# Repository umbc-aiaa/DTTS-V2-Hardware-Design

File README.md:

# DTTS V2

This repo houses the hardware design and associated documentation for the SUAS Dynamic Thrust Test Stand(DTTS) V2.
The new board is designed to be more intuitive to use and more robust against failures like over voltage, shorts, etc.
The V2 board also integrates all sensors and ICs in a single solution.

## System Diagram
```mermaid
graph LR;
LC[<b>Load Cell</b></br>Uses a Wheatstone Bridge to provide a differential voltage signal to the ADC.];
CS[<b>Current Sensor</b></br>Current sensing is implemented with a shunt resistor with differential input feeding into the ADC.];
VS[<b>Voltage Sensor</b></br>Voltage sensing circuit is implemented as a simple resistor voltage divider.];
ADC["<b>Analog-to-Digital Converter (ADC)</b></br>Converts single mode and differential analog signals into a digital format."];
MC[<b>ESP32 S3 WROOM 1</b></br>Controls esc for the motor, collects measurements, and communcates them over WiFi.];
ESC[<b>Electronic Speed Controller</b><br />Converts DC from battery to 3-phase AC for motor.]

GUI[<b>Front End UI</b></br>A front end GUI collects measurements and makes user interaction simple.];

LC --> ADC;
CS --> ADC;
VS --> ADC;

ADC --> MC;

MC -- PWM --> ESC;

GUI <== WiFi ==> MC;

ADC ~~~ GUI;
```

## Working Specs
- Battery Voltage $\leq$ 50 V.
- Max ESC Current $\leq$ 90 A.
- Using 6 AWG wire for battery.
- Must at minimum measure battery voltage, batter to ESC current, and Motor Thrust
- All circuitry must run off of a single battery -- the one plugged into the ESC
- Preferable to have auto-trimming and gain calibration on voltage sense circuity.

## Component Selection (Draft!)

### Power Supply
There are some different approaches to this. If we were using a seperate battery for this, then we could have just used a linear regulator, but if we want to use the motor battery, this voltage may range from 12 to 60 V. So we probably need to use a buck converter. We could also use a hybrid design (i.e. 12-60V input down to 4.5V with a buck converter and 4.5V to 3.3V with an LDO). This may complicate things a little, but it's a very good choice in terms of noise and is also fairly efficient.

1. ~~[Diodes Incorporated AP66200](https://www.diodes.com/assets/Datasheets/AP66200.pdf) Buck controller.~~
2. [TI LMR51625](https://www.ti.com/lit/ds/symlink/lmr51625.pdf?ts=1742888310253&ref_url=https%253A%252F%252Fwww.ti.com%252Fsitesearch%252Fen-us%252Fdocs%252Funiversalsearch.tsp%253FlangPref%253Den-US%2526nr%253D3%2526searchTerm%253DLMR51625XDDCR) Buck Controller (preferred).
  a. Also, if using TI ICs for power conversion, check out [Webench Designer](https://webench.ti.com/power-designer/)

**All regulated power rails must have a zener diode of appropriate voltage to pull lines down if they have too high of a voltage.**
We should run some simulations to ensure the zener diode is enough for protecting regulated lines if battery is shorted to them or if
we need to have something else. We may also want to consider adding a fuse to the power rail since the zener diode will short to ground
and pull a lot of current.

## Voltage Protection on Signal Pins
For signal pins, zener diodes may work, but there are options for more precise control like Schottkey diodes. These can also provide reverse polarity protection if configured correctly, so this is the solution we will use. Here are some options for diodes that may work. The Rohm diode has a lower forward drop, which is good for protecting against over-voltage, but it has a low reverse voltage rating which is worse for reverse-polarity protection. The opposite is true for the Toshiba diode. We may need to look for other diodes that have the adequate reverse voltage rating(60V) and a low drop(ideally $\leq$ 300mV).
1. [Toshiba CUS10S30 Schottkey Diodes](https://toshiba.semicon-storage.com/info/CUS10S30_datasheet_en_20140407.pdf?did=14077&prodName=CUS10S30) for signal over-voltage protection.\
  a. [Rohm RB520CM-60 Schottkey Diode](https://fscdn.rohm.com/en/products/databook/datasheet/discrete/diode/schottky_barrier/rb520cm-60t2r-e.pdf) Alternative to (1) with higher reverse voltage

### Analog to Digital Converter
This component converts analog voltages(i.e. voltages that are not strictly interpretted as a `0` or a `1`) into a digital format(i.e. `0`'s and `1`'s). This allows software on the esp32 to read and store analog voltages as numbers or percents and communicate these values over WiFi or another transport medium to the GUI for the user. Since we are using a load cell, this needs a sensative ADC, and hence we choose to use a 24-bit chip. These are some options worth considering:

1. [Microchip MCP3564R](https://ww1.microchip.com/downloads/aemDocuments/documents/APID/ProductDocuments/DataSheets/MCP3561_2_4R-Data-Sheet-DS200006391C.pdf) has four channels, meaning we can use this for all three sensors (battery voltage, battery current, and motor thrust).

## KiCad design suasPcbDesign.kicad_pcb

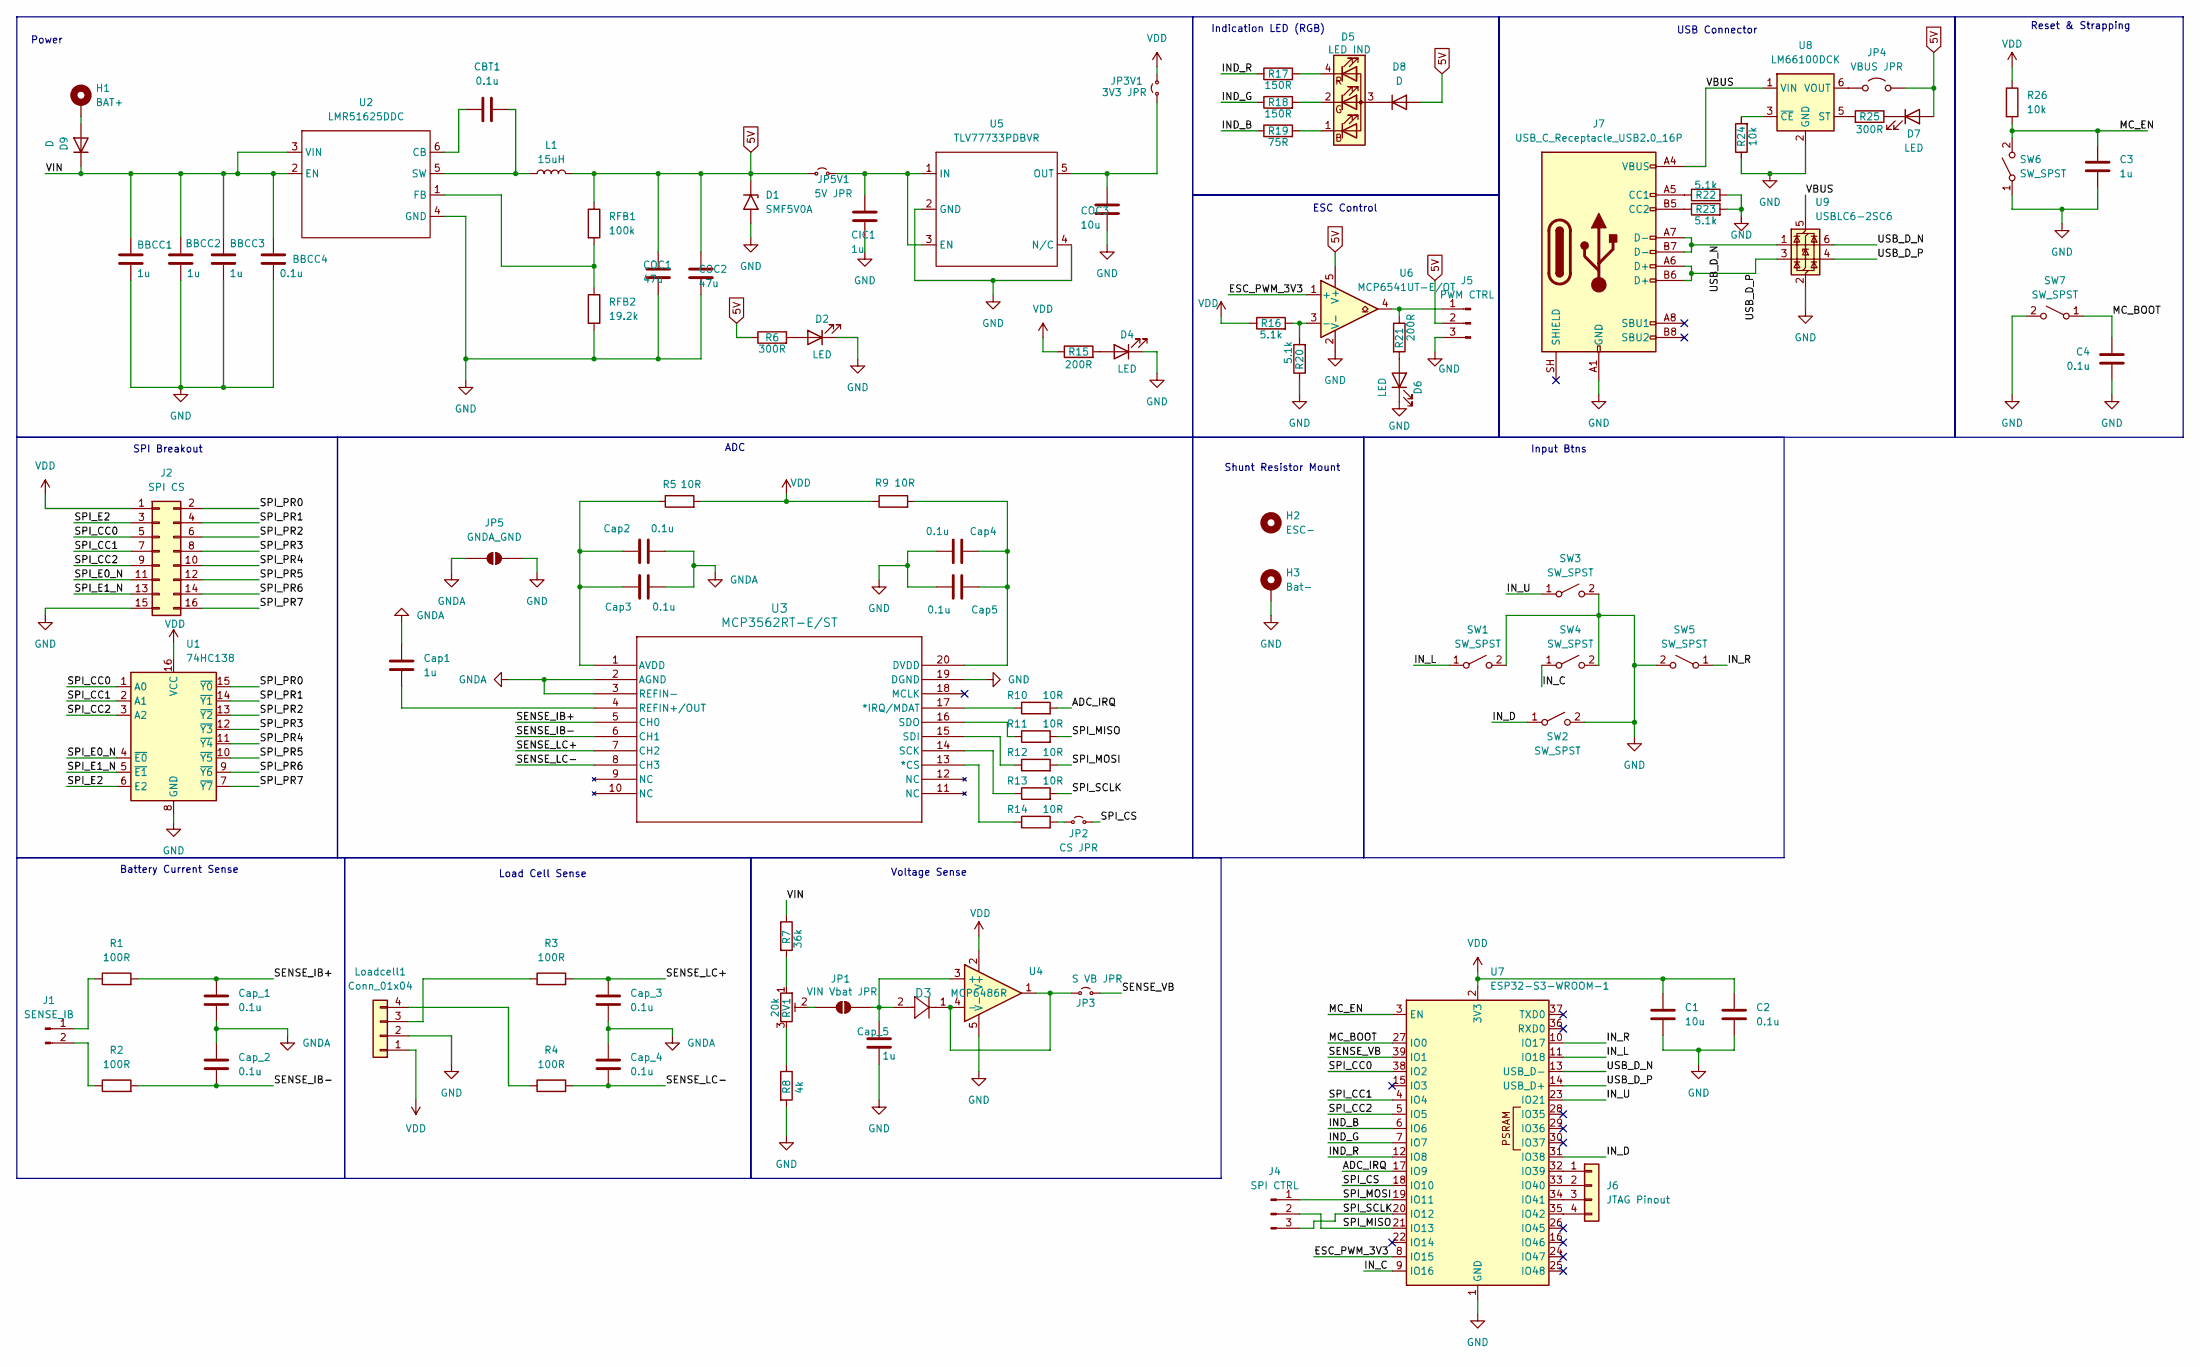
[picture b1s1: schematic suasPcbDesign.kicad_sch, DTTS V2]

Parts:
BBCC1, BBCC2, BBCC3: 1u; C_0603_1608Metric_Pad1.08x0.95mm_HandSolder
BBCC4: 0.1u; C_0603_1608Metric_Pad1.08x0.95mm_HandSolder
C1: 10u; C_0603_1608Metric_Pad1.08x0.95mm_HandSolder
C2, C4: 0.1u; C_0603_1608Metric_Pad1.08x0.95mm_HandSolder
C3: 1u; C_0603_1608Metric_Pad1.08x0.95mm_HandSolder
CBT1: 0.1u; C_0603_1608Metric_Pad1.08x0.95mm_HandSolder
CIC1: 1u; C_0603_1608Metric_Pad1.08x0.95mm_HandSolder
COC1, COC2: 47u; C_0603_1608Metric_Pad1.08x0.95mm_HandSolder
COC3: 10u; C_0603_1608Metric_Pad1.08x0.95mm_HandSolder
Cap1: 1u; C_0603_1608Metric_Pad1.08x0.95mm_HandSolder
Cap2, Cap3, Cap4, Cap5: 0.1u; C_0603_1608Metric_Pad1.08x0.95mm_HandSolder
Cap_1, Cap_2, Cap_3, Cap_4: 0.1u; C_0603_1608Metric_Pad1.08x0.95mm_HandSolder
Cap_5: 1u; C_0603_1608Metric_Pad1.08x0.95mm_HandSolder
D1: SMF5V0A; D_SOD-123
D2, D4, D6, D7: LED; LED_0603_1608Metric_Pad1.05x0.95mm_HandSolder
D3: CUS520_H3F; USC_TOS
D5: LED IND; LED_D5.0mm-4_RGB
D8, D9: D; D_SMA-SMB_Universal_Handsoldering
H1: BAT+; 7770 Keystone Electronics PC SCREW TERMINALS
H2: ESC-; MountingHole_6.3mm_M6_DIN965
H3: Bat-; MountingHole_6.3mm_M6_Pad_Via
J1: SENSE_IB; SolderWire-1sqmm_1x02_P5.4mm_D1.4mm_OD2.7mm
J2: SPI CS; PinHeader_2x08_P2.54mm_Vertical
J4: SPI CTRL; PinHeader_1x03_P2.54mm_Vertical
J5: PWM CTRL; PinHeader_1x03_P2.54mm_Vertical
J6: JTAG Pinout; PinHeader_1x04_P2.54mm_Vertical
J7: USB_C_Receptacle_USB2.0_16P; USB_C_Receptacle_GCT_USB4105-xx-A_16P_TopMnt_Horizontal
JP1: VIN Vbat JPR; SolderJumper-2_P1.3mm_Open_Pad1.0x1.5mm
JP2: CS JPR; TestPoint_2Pads_Pitch2.54mm_Drill0.8mm
JP3: S VB JPR; TestPoint_2Pads_Pitch2.54mm_Drill0.8mm
JP3V1: 3V3 JPR; TestPoint_2Pads_Pitch2.54mm_Drill0.8mm
JP4: VBUS JPR; TestPoint_2Pads_Pitch2.54mm_Drill0.8mm
JP5: GNDA_GND; SolderJumper-2_P1.3mm_Open_Pad1.0x1.5mm
JP5V1: 5V JPR; TestPoint_2Pads_Pitch2.54mm_Drill0.8mm
L1: 15uH; L_APV_APH1050
Loadcell1: Conn_01x04; PinHeader_1x04_P2.54mm_Vertical
R1, R2, R3, R4: 100R; R_0603_1608Metric_Pad0.98x0.95mm_HandSolder
R5, R9, R10, R11, R12, R13, R14: 10R; R_0603_1608Metric_Pad0.98x0.95mm_HandSolder
R6, R25: 300R; R_0603_1608Metric_Pad0.98x0.95mm_HandSolder
R7: 36k; R_0603_1608Metric_Pad0.98x0.95mm_HandSolder
R8: 4k; R_0603_1608Metric_Pad0.98x0.95mm_HandSolder
R15, R21: 200R; R_0603_1608Metric_Pad0.98x0.95mm_HandSolder
R16, R20, R22, R23: 5.1k; R_0603_1608Metric_Pad0.98x0.95mm_HandSolder
R17, R18: 150R; R_0603_1608Metric_Pad0.98x0.95mm_HandSolder
R19: 75R; R_0603_1608Metric_Pad0.98x0.95mm_HandSolder
R24, R26: 10k; R_0603_1608Metric_Pad0.98x0.95mm_HandSolder
RFB1: 100k; R_0603_1608Metric_Pad0.98x0.95mm_HandSolder
RFB2: 19.2k; R_0603_1608Metric_Pad0.98x0.95mm_HandSolder
RV1: 20k; Potentiometer_Bourns_3386P_Vertical
SW1, SW2, SW3, SW4, SW5, SW6, SW7: SW_SPST; SW_PUSH_1P1T_6x3.5mm_H4.3_APEM_MJTP1243
U1: 74HC138; TSSOP-16_4.4x5mm_P0.65mm
U2: LMR51625DDC; TSOT-23-6_HandSoldering
U3: MCP3562RT-E/ST; TSSOP-20_4.4x6.5mm_P0.65mm
U4: MCP6486R; SOT-23-5_HandSoldering
U5: TLV77733PDBVR; SOT-23-5_HandSoldering
U6: MCP6541UT-E/OT; SOT-23-5_HandSoldering
U7: ESP32-S3-WROOM-1
U8: LM66100DCK; SOT-363_SC-70-6
U9: USBLC6-2SC6; SOT-23-6

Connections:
5V: COC1.1, COC2.1, D1.1 (A1), D7.2 (A), D8.2 (A), J5.2, JP4.2 (B), JP5V1.1 (A), L1.2, R6.1, RFB1.1, U6.5 (V+)
/ADC_IRQ: R10.2, U7.17 (IO9)
/ESC_PWM_3V3: U6.1 (+), U7.8 (IO15)
/IND_B: R19.1, U7.6 (IO6)
/IND_G: R18.1, U7.7 (IO7)
/IND_R: R17.1, U7.12 (IO8)
/IN_C: SW4.1 (A), U7.9 (IO16)
/IN_D: SW2.1 (A), U7.31 (IO38)
/IN_L: SW1.1 (A), U7.11 (IO18)
/IN_R: SW5.1 (A), U7.10 (IO17)
/IN_U: SW3.1 (A), U7.23 (IO21)
/MC_BOOT: C4.1, SW7.1 (A), U7.27 (IO0)
/MC_EN: C3.1, R26.2, SW6.2 (B), U7.3 (EN)
/SENSE_IB+: Cap_1.1, R1.2, U3.5 (CH0)
/SENSE_IB-: Cap_2.2, R2.2, U3.6 (CH1)
/SENSE_LC+: Cap_3.1, R3.2, U3.7 (CH2)
/SENSE_LC-: Cap_4.2, R4.2, U3.8 (CH3)
/SENSE_VB: JP3.2 (B), U7.39 (IO1)
/SPI_CC0: J2.5, U1.1 (A0), U7.38 (IO2)
/SPI_CC1: J2.7, U1.2 (A1), U7.4 (IO4)
/SPI_CC2: J2.9, U1.3 (A2), U7.5 (IO5)
/SPI_CS: JP2.2 (B), U7.18 (IO10)
/SPI_E0_N: J2.11, U1.4 (~E0)
/SPI_E1_N: J2.13, U1.5 (~E1)
/SPI_E2: J2.3, U1.6 (E2)
/SPI_MISO: J4.2, R11.2, U7.21 (IO13)
/SPI_MOSI: J4.1, R12.2, U7.19 (IO11)
/SPI_PR0: J2.2, U1.15 (~Y0)
/SPI_PR1: J2.4, U1.14 (~Y1)
/SPI_PR2: J2.6, U1.13 (~Y2)
/SPI_PR3: J2.8, U1.12 (~Y3)
/SPI_PR4: J2.10, U1.11 (~Y4)
/SPI_PR5: J2.12, U1.10 (~Y5)
/SPI_PR6: J2.14, U1.9 (~Y6)
/SPI_PR7: J2.16, U1.7 (~Y7)
/SPI_SCLK: J4.3, R13.2, U7.20 (IO12)
/USB_D_N: J7.A7 (D-), J7.B7 (D-), U7.13 (USB_D-), U9.1 (I/O1), U9.6 (I/O1)
/USB_D_P: J7.A6 (D+), J7.B6 (D+), U7.14 (USB_D+), U9.3 (I/O2), U9.4 (I/O2)
/VBUS: J7.A4 (VBUS), J7.A9 (VBUS), J7.B4 (VBUS), J7.B9 (VBUS), U8.1 (VIN), U9.5 (VBUS)
/VIN: BBCC1.1, BBCC2.1, BBCC3.1, BBCC4.1, D9.1 (K), R7.1, U2.2 (EN), U2.3 (VIN)
GND: BBCC1.2, BBCC2.2, BBCC3.2, BBCC4.2, C1.2, C2.2, C3.2, C4.2, CIC1.2, COC1.2, COC2.2, COC3.2, Cap4.2, Cap5.2, Cap_5.2, D1.2 (A2), D2.1 (K), D4.1 (K), D6.1 (K), H3.1 (1_1), J2.15, J5.3, J7.A1 (GND), J7.A12 (GND), J7.B1 (GND), J7.B12 (GND), JP5.2 (B), Loadcell1.2, R8.2, R20.1, R22.2, R23.2, R24.1, RFB2.2, SW1.2 (B), SW2.2 (B), SW3.2 (B), SW4.2 (B), SW5.2 (B), SW6.1 (A), SW7.2 (B), U1.8 (GND), U2.4 (GND), U3.19 (DGND), U4.5 (V-), U5.2 (GND), U5.4 (N/C), U6.2 (V-), U7.1 (GND), U7.40 (GND), U7.41 (GND), U8.2 (GND), U9.2 (GND)
GNDA: Cap1.2, Cap2.2, Cap3.2, Cap_1.2, Cap_2.1, Cap_3.2, Cap_4.1, JP5.1 (A), U3.2 (AGND), U3.3 (REFIN-)
unnamed: D2.2 (A), R6.2
unnamed: D4.2 (A), R15.2
unnamed: D5.3 (A), D8.1 (K)
unnamed: D5.1 (BK), R19.2
unnamed: D5.2 (GK), R18.2
unnamed: D5.4 (RK), R17.2
unnamed: D6.2 (A), R21.2
unnamed: D7.1 (K), R25.1
unnamed: D9.2 (A), H1.1 (1_1)
unnamed: J1.1, R1.1
unnamed: J1.2, R2.1
unnamed: J5.1, R21.1, U6.4
unnamed: J6.1, U7.32 (IO39)
unnamed: J6.2, U7.33 (IO40)
unnamed: J6.3, U7.34 (IO41)
unnamed: J6.4, U7.35 (IO42)
unnamed: J7.A5 (CC1), R22.1
unnamed: J7.B5 (CC2), R23.1
unnamed: JP1.1 (A), RV1.2
unnamed: Cap_5.1, D3.2, JP1.2 (B), U4.3 (+)
unnamed: JP2.1 (A), R14.2
unnamed: D3.1, JP3.1 (A), U4.1, U4.4 (-)
unnamed: COC3.1, JP3V1.1 (A), U5.5 (OUT)
unnamed: JP4.1 (A), U8.6 (VOUT)
unnamed: CIC1.1, JP5V1.2 (B), U5.1 (IN), U5.3 (EN)
unnamed: Loadcell1.3, R3.1
unnamed: Loadcell1.4, R4.1
unnamed: R7.2, RV1.1
unnamed: R8.1, RV1.3
unnamed: CBT1.1, U2.6 (CB)
unnamed: RFB1.2, RFB2.1, U2.1 (FB)
unnamed: CBT1.2, L1.1, U2.5 (SW)
unnamed: R14.1, U3.13 (*CS)
unnamed: R10.1, U3.17 (*IRQ/MDAT)
unnamed: Cap2.1, Cap3.1, R5.1, U3.1 (AVDD)
unnamed: Cap4.1, Cap5.1, R9.2, U3.20 (DVDD)
unnamed: Cap1.1, U3.4 (REFIN+/OUT)
unnamed: R13.1, U3.14 (SCK)
unnamed: R12.1, U3.15 (SDI)
unnamed: R11.1, U3.16 (SDO)
unnamed: R16.2, R20.2, U6.3 (-)
unnamed: R25.2, U8.5 (ST)
unnamed: R24.2, U8.3 (~CE)
VDD: C1.1, C2.1, J2.1, JP3V1.2 (B), Loadcell1.1, R5.2, R9.1, R15.1, R16.1, R26.1, U1.16 (VCC), U4.2 (V+), U7.2 (3V3)

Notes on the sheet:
SPI Breakout
Reset & Strapping
Voltage Sense
ESC Control
Shunt Resistor Mount
Load Cell Sense
Input Btns
Battery Current Sense
Power
Indication LED (RGB)
ADC
USB Connector

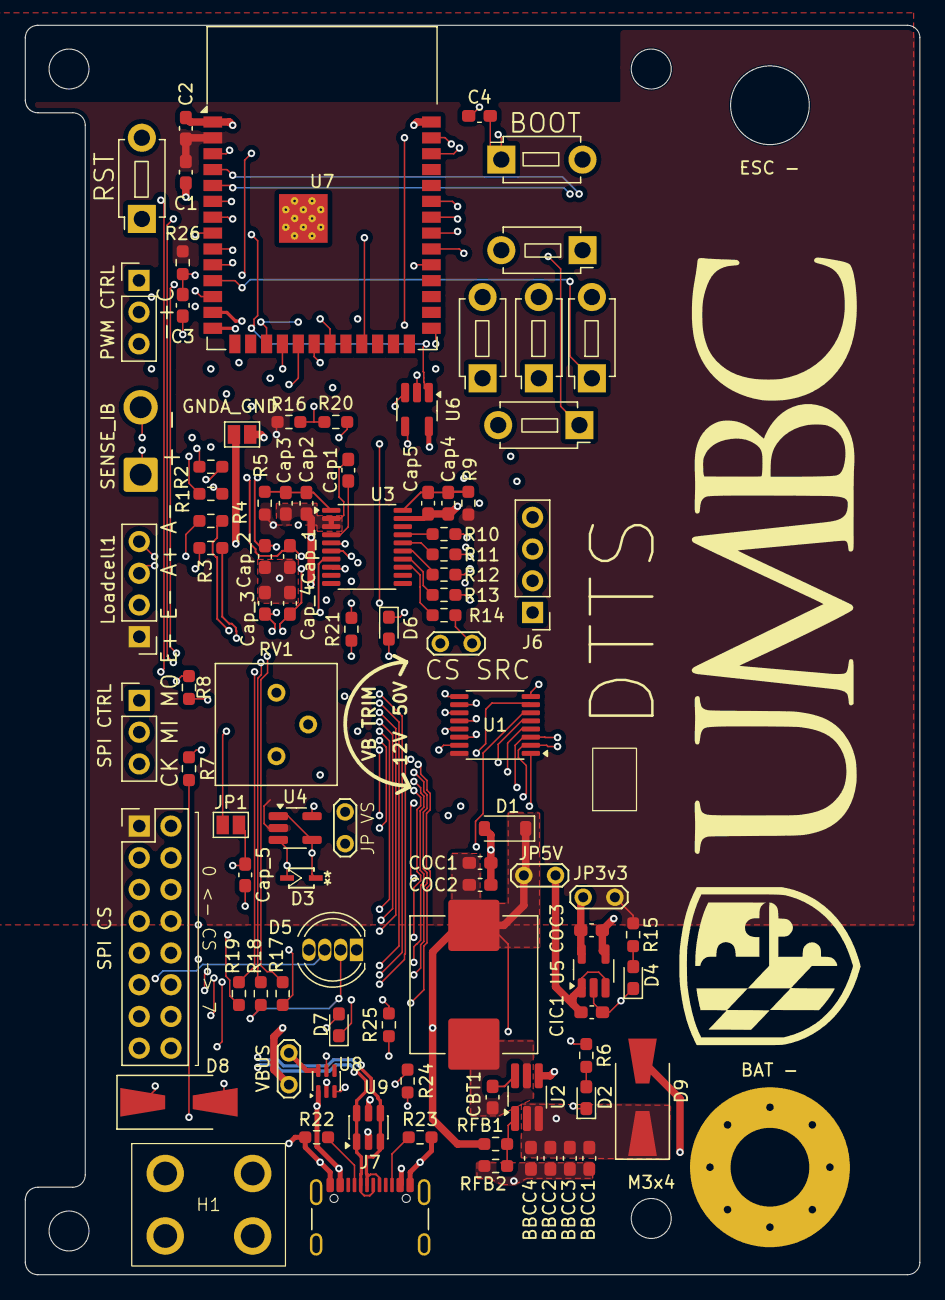
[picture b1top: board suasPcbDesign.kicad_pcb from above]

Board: 4 copper layers, 71.6 x 100.0 mm, 99 parts (0 on the bottom side), 86 nets.

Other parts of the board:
M3x1, M3x2, M3x3, M3x4: MountingHole_3.2mm_M3

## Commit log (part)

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2026-04-20 added buck converter schematic
2026-04-21 added LDO and microcontroller
2026-04-21 added in zener diode
2026-04-28 Added voltage divider
2026-04-28 Fixed voltage divider and added power to ADC
2026-04-28 added current sensor, finished ADC implementation, and added a battery symbol
2026-04-29 added load sensor
2026-04-29 added LCD display
2026-05-07 added lcd display pins
2026-05-08 added footprints to IC's
2026-05-09 added footprints
2026-05-23 corrected footprints with parts chosen from digikey
2026-06-07 configured board set up and rearranged pcb layout
2026-06-29 clean up design
2026-06-29 Added Mounting Holes For Shunt Resistor
    Added mounting holes for shunt resistor and connectors to go the ADC
2026-06-29 Add voltage protection circuitry
2026-06-29 Add indication lights
2026-06-29 Fix LED Type
2026-06-30 Simplify voltage clamping circuit for voltage sensor
2026-06-30 Organize schematic
2026-06-30 Replace trim pot
2026-06-30 Add decoupling caps to esp32 s3
